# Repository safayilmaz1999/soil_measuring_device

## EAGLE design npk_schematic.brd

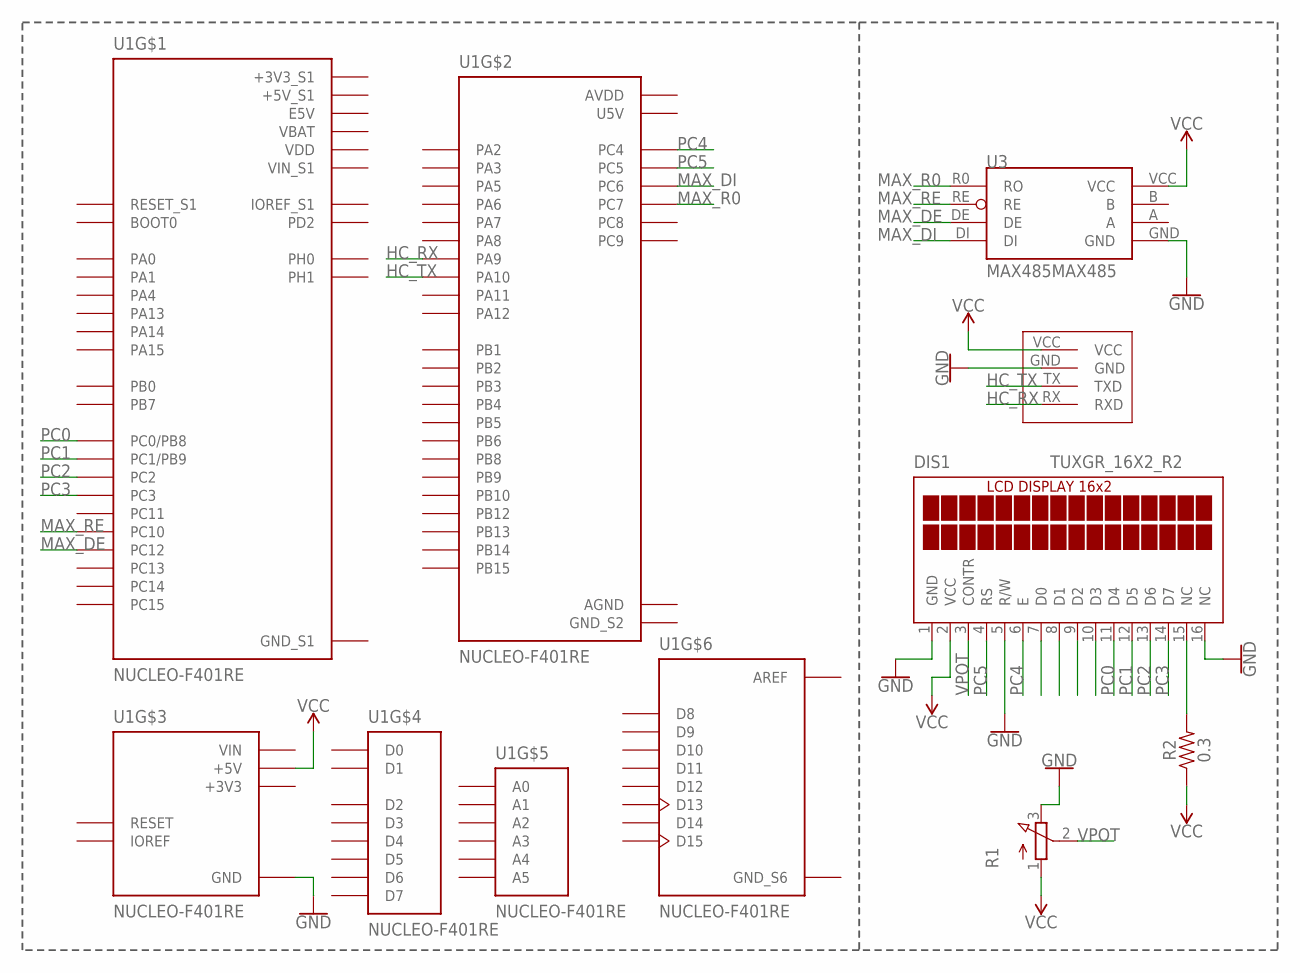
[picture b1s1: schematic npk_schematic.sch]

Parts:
DIS1: TUXGR_16X2_R2
R1: 3RP/1610N
R2: 0.3; 0805
U1: NUCLEO-F401RE; ST_NUCLEO-F401RE
U2: HC-06_ARDUıNO_BLUETOOTH; HC-06_ARDUINO_BLUETOOTH
U3: MAX485MAX485; DIL08

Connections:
+3V3: U1.+3V3@2 (+3V3)
+3V3_S1: U1.+3V3@1 (+3V3_S1)
+5V_S1: U1.+5V@1 (+5V_S1)
AGND: U1.AGND
AREF: U1.AVDD@2 (AREF)
AVDD: U1.AVDD@1 (AVDD)
E5V: U1.E5V
GND: DIS1.1 (GND), DIS1.5 (R/W), DIS1.16 (NC), R1.3 (E), U1.GND@4 (GND), U1.GND@6 (GND), U2.GND, U3.GND
GND_S1: U1.GND@1 (GND_S1), U1.GND@2 (GND_S1), U1.GND@3 (GND_S1), U1.GND@5 (GND_S1)
GND_S2: U1.GND@7 (GND_S2), U1.GND@8 (GND_S2)
GND_S6: U1.GND@9 (GND_S6)
HC_RX: U1.PA9@1 (PA9), U2.RX (RXD)
HC_TX: U1.PA10@1 (PA10), U2.TX (TXD)
MAX_DE: U1.PC12, U3.DE
MAX_DI: U1.PC6, U3.DI
MAX_R0: U1.PC7@1 (PC7), U3.R0 (RO)
MAX_RE: U1.PC10, U3.RE
unnamed: DIS1.15 (NC), R2.2
PC0: DIS1.11 (D4), U1.PC0@1 (PC0/PB8)
PC1: DIS1.12 (D5), U1.PC1@1 (PC1/PB9)
PC2: DIS1.13 (D6), U1.PC2
PC3: DIS1.14 (D7), U1.PC3
PC4: DIS1.6 (E), U1.PC4
PC5: DIS1.4 (RS), U1.PC5
U5V: U1.U5V
VBAT: U1.VBAT
VCC: DIS1.2 (VCC), R1.1 (A), R2.1, U1.+5V@2 (+5V), U2.VCC, U3.VCC
VDD: U1.VDD
VIN: U1.VIN@2 (VIN)
VIN_S1: U1.VIN@1 (VIN_S1)
VPOT: DIS1.3 (CONTR), R1.2 (S)

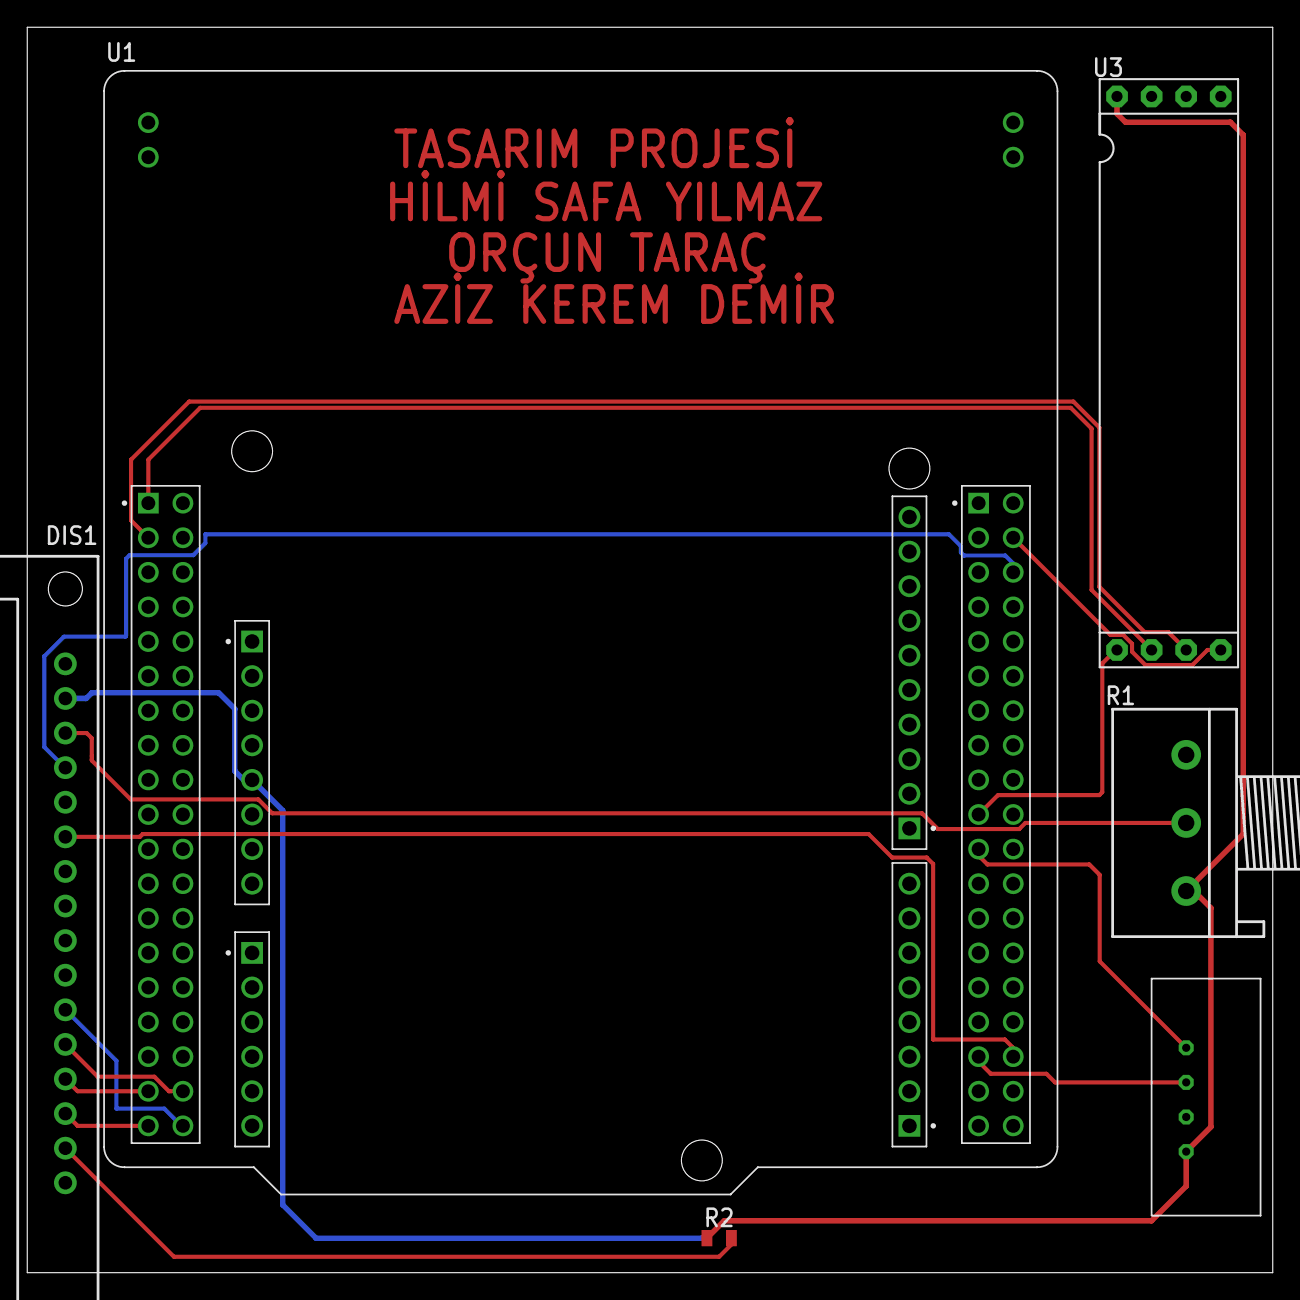
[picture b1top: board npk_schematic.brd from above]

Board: 2 copper layers, 91.4 x 91.4 mm, 6 parts (0 on the bottom side), 18 nets.

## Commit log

2022-02-25 upload

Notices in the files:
parts and their libraries:
SparkFun-Resistors: Licensing: Creative Commons ShareAlike 4.0 International - https://creativecommons.org/licenses/by-sa/4.0
